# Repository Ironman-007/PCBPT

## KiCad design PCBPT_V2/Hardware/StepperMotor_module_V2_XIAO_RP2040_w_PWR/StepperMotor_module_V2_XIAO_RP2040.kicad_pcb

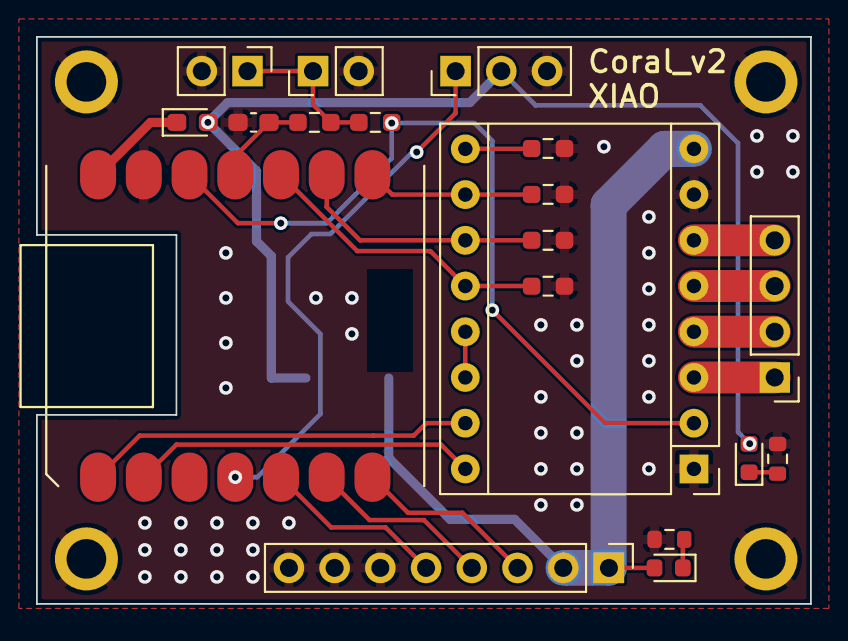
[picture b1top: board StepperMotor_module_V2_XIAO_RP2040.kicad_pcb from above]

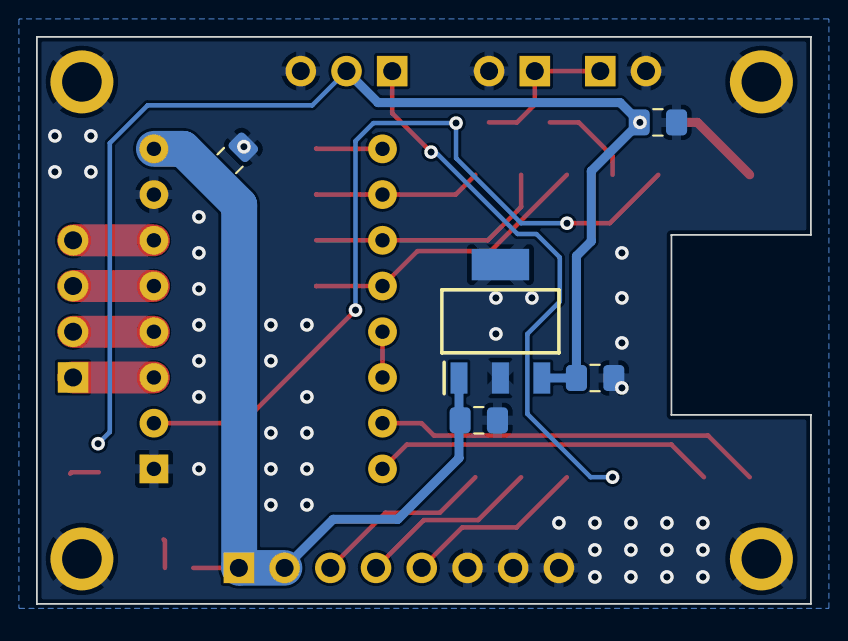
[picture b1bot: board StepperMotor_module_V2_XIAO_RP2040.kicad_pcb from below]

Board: 2 copper layers, 43.0 x 31.5 mm, 28 parts (5 on the bottom side), 24 nets.

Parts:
A1: Pololu_Breakout_A4988; Pololu_Breakout-16_15.2x20.3mm
C1, C5: 0.1uF; C_0805_2012Metric_Pad1.18x1.45mm_HandSolder
C2: 0.01uF; C_0603_1608Metric_Pad1.08x0.95mm_HandSolder
C3: 22uF; C_0805_2012Metric_Pad1.18x1.45mm_HandSolder
C4: 0.47uF; C_0805_2012Metric_Pad1.18x1.45mm_HandSolder
D1, D4: LED_Small_Filled; LED_0603_1608Metric
D2: Schottky; D_0603_1608Metric_Pad1.05x0.95mm_HandSolder
H1, H2, H3, H4: M2; MountingHole_2.2mm_M2_ISO7380_Pad
IC1: LM2940IMP-5.0_NOPB; SOT230P700X180-4N
J1: Conn_01x08_Pin; PinHeader_1x08_P2.54mm_Vertical
J3: Servo; PinHeader_1x03_P2.54mm_Vertical
J4: Limit Switch; PinHeader_1x04_P2.54mm_Vertical
J6, J7: Limit Switch; PinHeader_1x02_P2.54mm_Vertical
R1: 499K; R_0603_1608Metric_Pad0.98x0.95mm_HandSolder
R2, R3, R4, R11: 10K; R_0603_1608Metric_Pad0.98x0.95mm_HandSolder
R8, R10: 10k; R_0603_1608Metric
R12: 100; R_0603_1608Metric_Pad0.98x0.95mm_HandSolder
U1: MOUDLE-SEEEDUINO-XIAO; MOUDLE14P-SMD-2.54-21X17.8MM

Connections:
1A: A1.4 (1A), J4.2
1B: A1.3 (1B), J4.1
2A: A1.5 (2A), J4.3
2B: A1.6 (2B), J4.4
+3V3: A1.2 (VDD), R11.1, U1.12 (3V3)
/A4988_Module/M_EN: A1.9 (~ENABLE), R1.1
DIR: A1.16 (DIR), U1.2 (PA4_A1_D1)
GND: A1.1 (GND), A1.7 (GND), C1.2, C2.2, C3.2, C4.2, C5.2, H1.1, H2.1, H3.1, H4.1, IC1.2 (GND_1), IC1.4 (GND_2), J1.6, J1.7, J1.8, J3.3, J6.2, J7.2, R1.2, R2.2, R3.2, R4.2, R8.2, R10.2, U1.13 (GND)
GPIO: J1.3, U1.7 (PB08_A6_D6_TX)
LIMIT_SW_0: C2.1, R12.1, U1.11 (PA6_A10_D10_MOSI)
MS1: A1.10 (MS1), R2.1, U1.8 (PB09_A7_D7_RX)
MS2: A1.11 (MS2), R3.1, U1.9 (PA7_A8_D8_SCK)
MS3: A1.12 (MS3), R4.1, U1.10 (PA5_A9_D9_MISO)
unnamed: A1.13 (~RESET), A1.14 (~SLEEP)
unnamed: D1.1 (K), R8.1
unnamed: D2.1 (K), U1.14 (5V)
unnamed: D4.1 (K), R10.1
unnamed: J6.1, J7.1, R11.2, R12.2
PWM_S: J3.1, U1.4 (PA11_A3_D3)
SCL: J1.4, U1.6 (PA9_A5_D5_SCL)
SDA: J1.5, U1.5 (PA8_A4_D4_SDA)
STEP: A1.15 (STEP), U1.1 (PA02_A0_D0)
VCC: C3.1, C5.1, D1.2 (A), D2.2 (A), IC1.3 (OUT), J3.2
VPP: A1.8 (VMOT), C1.1, C4.1, D4.2 (A), IC1.1 (IN), J1.1, J1.2
